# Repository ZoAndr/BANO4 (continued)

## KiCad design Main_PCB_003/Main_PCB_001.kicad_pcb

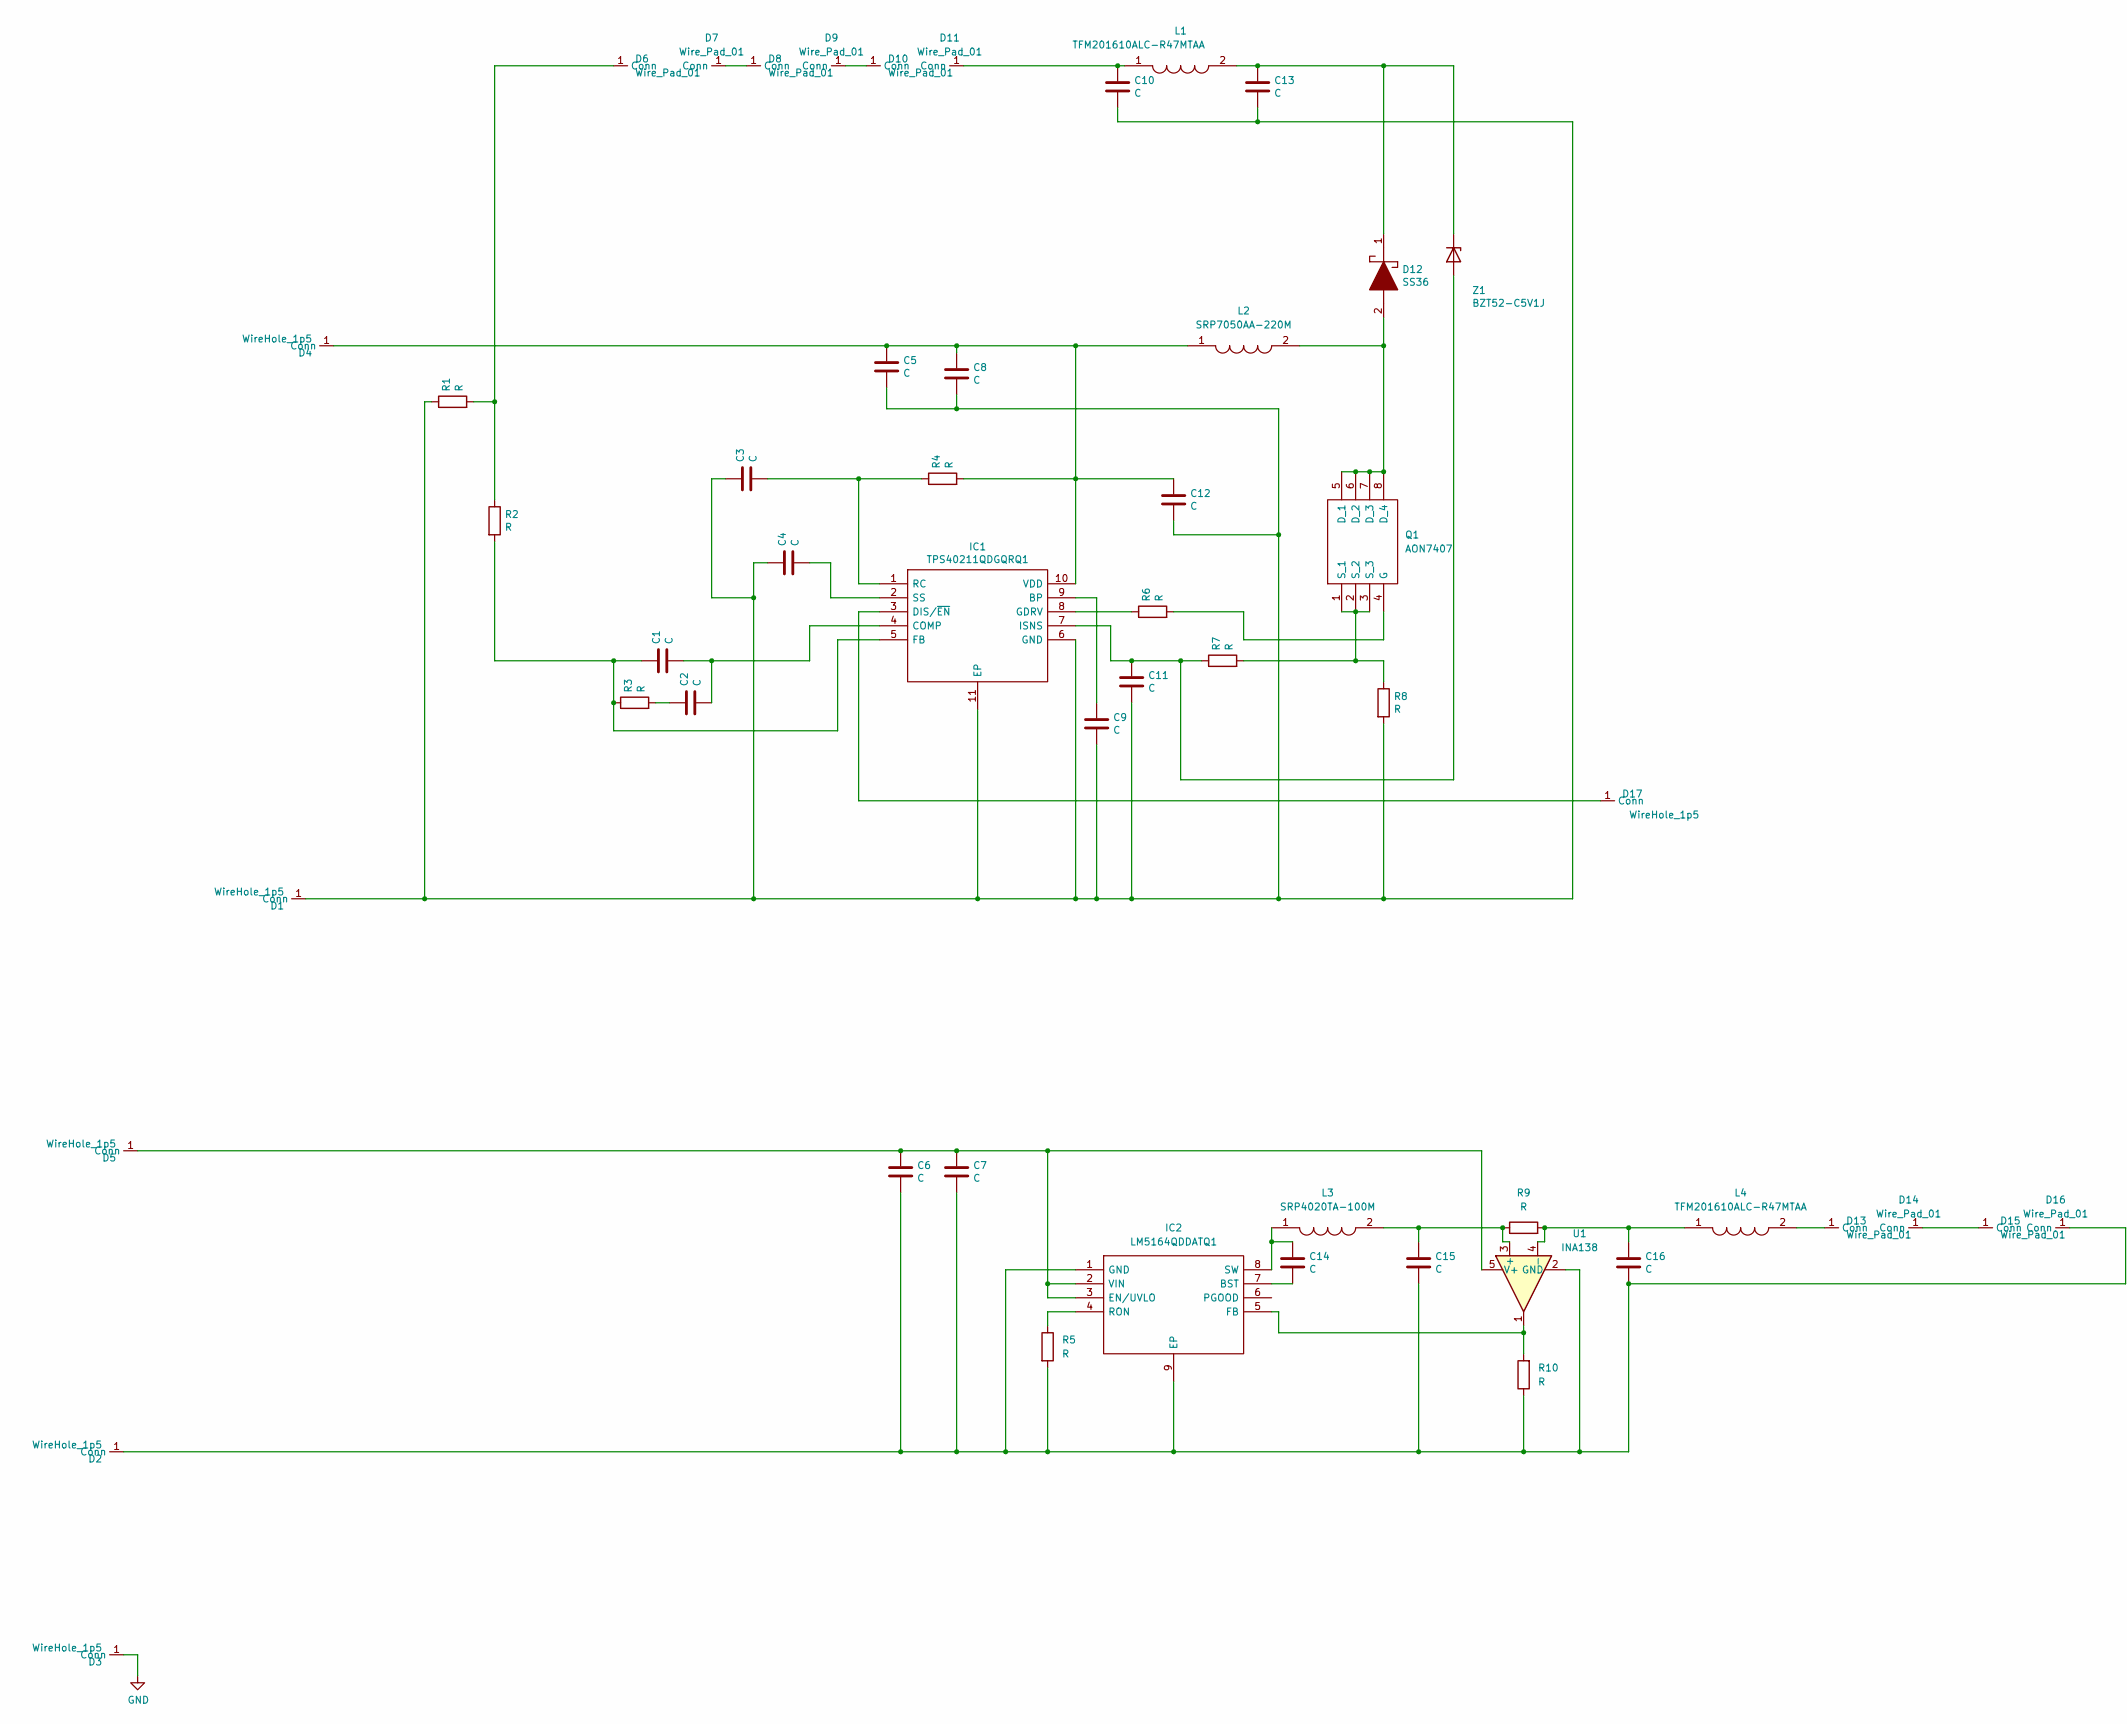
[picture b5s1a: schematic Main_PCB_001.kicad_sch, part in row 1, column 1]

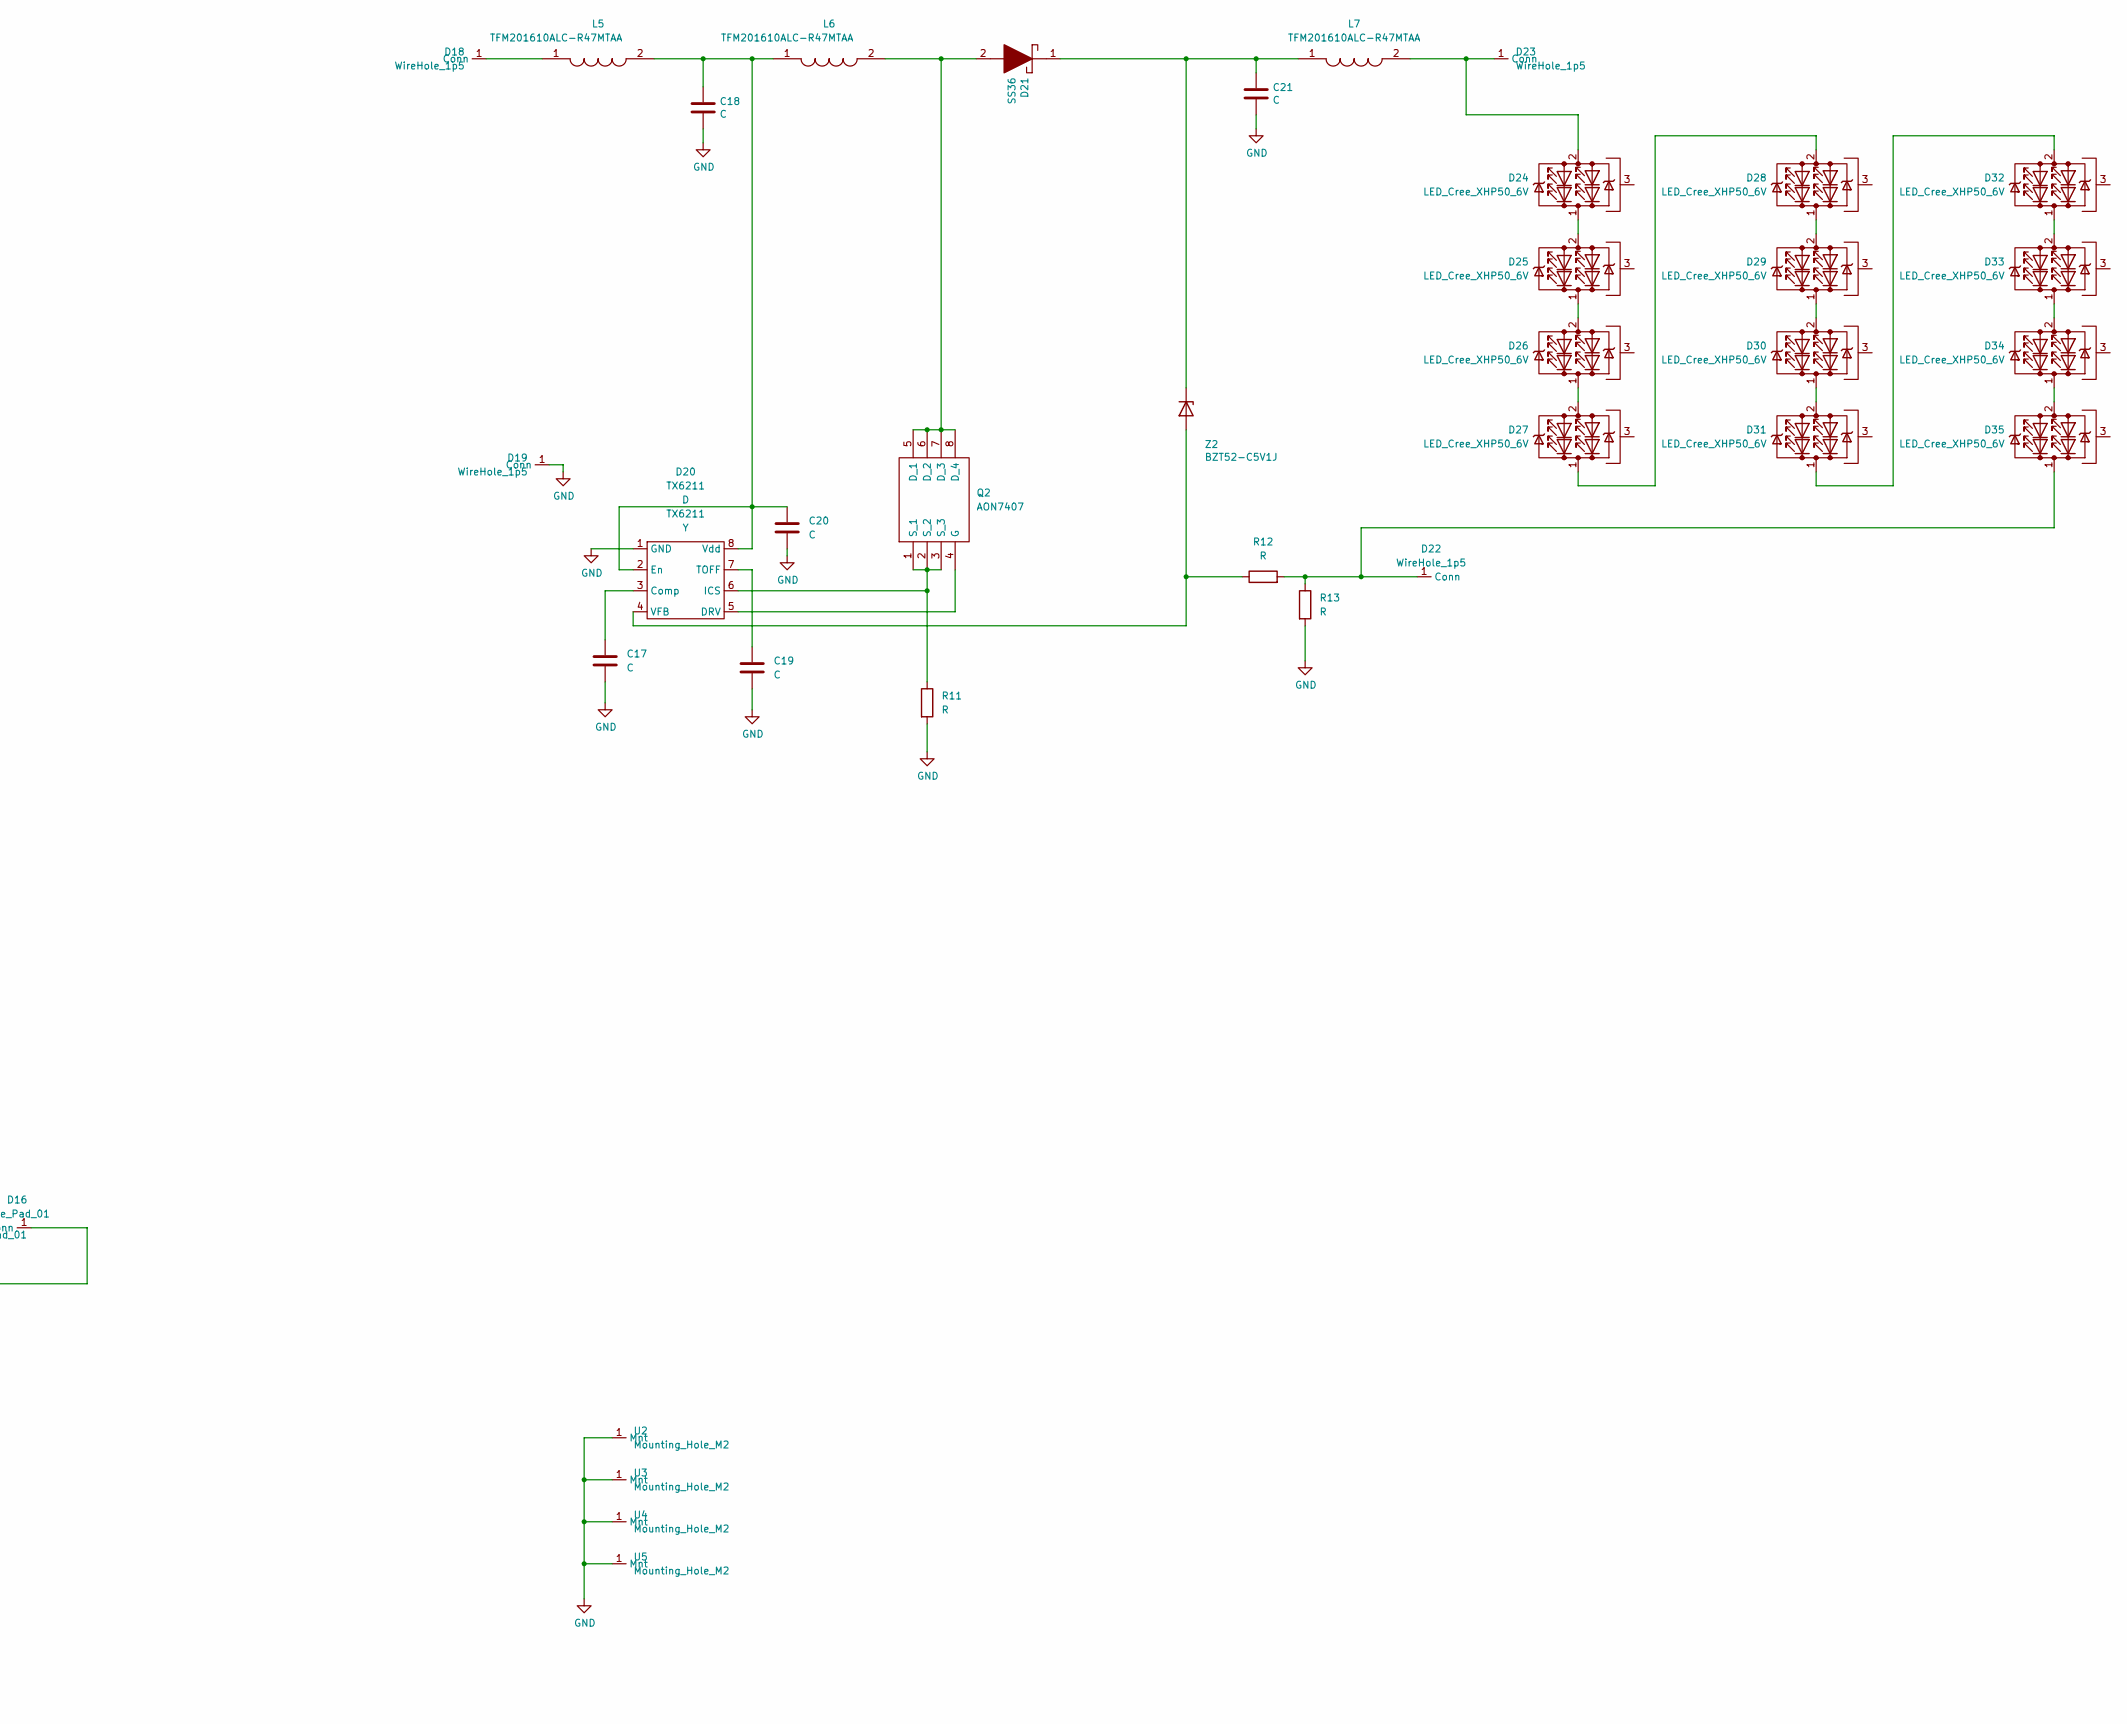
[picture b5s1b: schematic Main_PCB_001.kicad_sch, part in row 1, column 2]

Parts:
C1, C2, C3, C4, C9, C11, C17, C19, C20: C; C_0805_2012Metric_Pad1.18x1.45mm_HandSolder
C5, C6, C10, C12: C; C_0603_1608Metric_Pad1.08x0.95mm_HandSolder
C7, C8, C13, C15, C16, C18, C21: C; C_1206_3216Metric_Pad1.33x1.80mm_HandSolder
C14: C; C_0402_1005Metric_Pad0.74x0.62mm_HandSolder
D1, D2, D3, D4, D5, D17, D18, D19, D22, D23: WireHole_1p5; WireHole_1p2
D6, D7, D8, D9, D10, D11, D13, D14, D15, D16: Wire_Pad_01; Wire_Hole_1mm
D12, D21: SS36; SODFL4626X120N; Manufacturer_Part_Number SS36
D20: TX6211
D24, D25, D26, D27, D28, D29, D30, D31, D32, D33, D34, D35: LED_Cree_XHP50_6V; LED_Cree-XHP50_6V
IC1: TPS40211QDGQRQ1; SOP50P490X110-11N; Manufacturer_Part_Number TPS40211QDGQRQ1; Mouser Part Number 595-TPS40211QDGQRQ1
IC2: LM5164QDDATQ1; SOIC127P600X170-9N; Manufacturer_Part_Number LM5164QDDATQ1; Mouser Part Number 595-LM5164QDDATQ1
L1, L4, L5, L7: TFM201610ALC-R47MTAA; INDC2016X80N; Manufacturer_Part_Number TFM201610ALC-R47MTAA; Mouser Part Number 810-TFM201610ALCR47M
L2: SRP7050AA-220M; INDPM5752X300N; Manufacturer_Part_Number SRP7050AA-220M; Mouser Part Number 652-SRP7050AA-220M
L3: SRP4020TA-100M; INDPM4441X200N; Manufacturer_Part_Number SRP4020TA-100M; Mouser Part Number 652-SRP4020TA-100M
L6: TFM201610ALC-R47MTAA; INDPM5752X300N; Manufacturer_Part_Number TFM201610ALC-R47MTAA; Mouser Part Number 810-TFM201610ALCR47M
Q1, Q2: AON7407; DFN_3X3_EP; Manufacturer_Part_Number AON7407
R1, R2, R3, R4, R6, R7, R8, R11, R12, R13: R; R_0805_2012Metric_Pad1.20x1.40mm_HandSolder
R5, R9, R10: R; R_0402_1005Metric_Pad0.72x0.64mm_HandSolder
U1: INA138; SOT-23-5
U2, U3, U4, U5: Mounting_Hole_M2; Hole_screw_M1p2
Z1, Z2: BZT52-C5V1J; D_SOD-323F; Manufacturer_Part_Number BZT52-C5V1J; Mouser Part Number N/A

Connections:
GND: C17.2, C18.2, C19.2, C20.2, C21.2, D3.1 (Conn), D19.1 (Conn), D20.1 (GND), R11.2, R13.2, U2.1 (Mnt), U3.1 (Mnt), U4.1 (Mnt), U5.1 (Mnt)
unnamed: C1.1, IC1.5 (FB), R2.2, R3.1
unnamed: C1.2, C2.2, IC1.4 (COMP)
unnamed: C2.1, R3.2
unnamed: C3.2, IC1.1 (RC), R4.1
unnamed: C4.2, IC1.2 (SS)
unnamed: C6.1, C7.1, D5.1 (Conn), IC2.2 (VIN), IC2.3 (EN/UVLO), U1.5 (V+)
unnamed: C9.1, IC1.9 (BP)
unnamed: C10.1, D11.1 (Conn), L1.1
unnamed: C3.1, C4.1, C5.2, C8.2, C9.2, C10.2, C11.2, C12.2, C13.2, D1.1 (Conn), IC1.6 (GND), IC1.11 (EP), R1.1, R8.2
unnamed: C11.1, IC1.7 (ISNS), R7.1, Z1.2 (A)
unnamed: C5.1, C8.1, C12.1, D4.1 (Conn), IC1.10 (VDD), L2.1, R4.2
unnamed: C13.1, D12.1, L1.2, Z1.1 (K)
unnamed: C14.1, IC2.8 (SW), L3.1
unnamed: C14.2, IC2.7 (BST)
unnamed: C15.1, L3.2, R9.1, U1.3 (+)
unnamed: C6.2, C7.2, C15.2, C16.2, D2.1 (Conn), D16.1 (Conn), IC2.1 (GND), IC2.9 (EP), R5.2, R10.1, U1.2 (GND)
unnamed: C16.1, L4.1, R9.2, U1.4 (-)
unnamed: C17.1, D20.3 (Comp)
unnamed: C18.1, C20.1, D20.2 (En), D20.8 (Vdd), L5.2, L6.1
unnamed: C19.1, D20.7 (TOFF)
unnamed: C21.1, D21.1, L7.1, Z2.1 (K)
unnamed: D6.1 (Conn), R1.2, R2.1
unnamed: D7.1 (Conn), D8.1 (Conn)
unnamed: D9.1 (Conn), D10.1 (Conn)
unnamed: D12.2, L2.2, Q1.5 (D_1), Q1.6 (D_2), Q1.7 (D_3), Q1.8 (D_4)
unnamed: D13.1 (Conn), L4.2
unnamed: D14.1 (Conn), D15.1 (Conn)
unnamed: D17.1 (Conn), IC1.3 (DIS/~EN)
unnamed: D18.1 (Conn), L5.1
unnamed: D20.4 (VFB), R12.1, Z2.2 (A)
unnamed: D20.5 (DRV), Q2.4 (G)
unnamed: D20.6 (ICS), Q2.1 (S_1), Q2.2 (S_2), Q2.3 (S_3), R11.1
unnamed: D21.2, L6.2, Q2.5 (D_1), Q2.6 (D_2), Q2.7 (D_3), Q2.8 (D_4)
unnamed: D22.1 (Conn), D35.1 (K), R12.2, R13.1
unnamed: D23.1 (Conn), D24.2 (A), L7.2
unnamed: D24.1 (K), D25.2 (A)
unnamed: D25.1 (K), D26.2 (A)
unnamed: D26.1 (K), D27.2 (A)
unnamed: D27.1 (K), D28.2 (A)
unnamed: D28.1 (K), D29.2 (A)
unnamed: D29.1 (K), D30.2 (A)
unnamed: D30.1 (K), D31.2 (A)
unnamed: D31.1 (K), D32.2 (A)
unnamed: D32.1 (K), D33.2 (A)
unnamed: D33.1 (K), D34.2 (A)
unnamed: D34.1 (K), D35.2 (A)
unnamed: IC1.8 (GDRV), R6.1
unnamed: IC2.4 (RON), R5.1
unnamed: IC2.5 (FB), R10.2, U1.1
unnamed: Q1.1 (S_1), Q1.2 (S_2), Q1.3 (S_3), R7.2, R8.1
unnamed: Q1.4 (G), R6.2

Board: 4 copper layers, 87 parts (0 on the bottom side), 52 nets, no tracks yet.
